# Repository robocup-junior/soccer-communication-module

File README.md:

# RCJ Soccer Communication Module

A small referee-to-robot interface for **RoboCupJunior Soccer**. A referee controls the module over **Bluetooth Low Energy (BLE)** from the mobile app, and the module relays the live match state — **PLAY, STOP, penalty, half-time, game over** — to the robot or host controller over simple digital outputs, UART, or USB serial.

The current module (board **V7 / 2026**) is built around an **ESP32-C5** and includes an OLED display, three buttons, an RGB LED, a buzzer, a USB-C port for power & flashing, and an on-board **supercapacitor** backup. It does **not** count toward the robot weight limit.

> 📦 **Got an older 2024 board?** That one uses an ESP32-**C6** — see [Legacy 2024 (ESP32-C6) modules](#-legacy-2024-esp32-c6-modules) below.

---

## 🚀 Get started

**1. Install the referee app** — Android, free on Google Play:

**➡️ [RCJ Soccer app on Google Play](https://play.google.com/store/apps/details?id=com.robocup.rcj_soccer)**

**2. Flash the module** — easiest is the **web flasher**, nothing to install:

**➡️ [Web flasher](https://robocup-junior.github.io/soccer-communication-module/)** — connect the module over USB-C and flash straight from your browser.

> The web flasher uses the Web Serial API, so use **desktop Chrome or Edge**.

**3. Wire it to your robot** — power the module from the robot battery and read one start/stop signal (see [below](#-connecting-it-to-your-robot)).

---

## 📱 Using the app

The app connects to the module over BLE and drives the whole match. The interaction pattern:

- **Double-click** for actions — e.g. double-click a robot to start/stop it, or to issue a penalty.
- **Hold** for settings — e.g. hold a robot button for connection settings.
- **Start/stop** resets all timers and starts/stops all robots at once.
- **Score:** double-click a score to add a point; hold the score number for −1.

The app's source code lives in its own repository: **[robocup-junior/soccer-referee-app](https://github.com/robocup-junior/soccer-referee-app)**.

---

## 🔌 Connecting it to your robot

### Read the start/stop signal (pick one method)

The robot must respond to the start/stop signal for the entire game. Use **one** of the following methods and react whenever the state changes:

| Method         | Pin                            | PLAY / GO        | STOP        |
|----------------|--------------------------------|------------------|-------------|
| **Output pin** | `OUT1` or `OUT2`               | **3.3 V** (HIGH) | **0 V** (LOW) |
| **UART**       | `TX0` (UART0 on the U3 header) | sends `PLAY`     | sends `STOP` |
| **USB serial** | USB-C                          | sends `PLAY`     | sends `STOP` |

Both outputs carry the same 3.3 V logic-level signal. For 5 V robot inputs, add a level shifter before the robot. Always share **GND** with the robot controller — never connect VIN to a robot GPIO or to the 3.3 V pin.

For a Raspberry Pi or another USB host, connect the module's USB-C port to the host's USB-A port. The ESP32-C5 enumerates as a serial device, typically `/dev/ttyACM0`, and prints one line (`PLAY` or `STOP`) whenever the referee app changes the match state.

On Linux, you can check the USB serial output with:

```sh
stty -F /dev/ttyACM0 115200 raw -echo
cat /dev/ttyACM0
```

The onboard buzzer gives a short confirmation beep whenever the referee app changes the match state.
The RGB status LED is dimmed green in PLAY and dimmed red when the robot output is stopped.

### Power it

Power the module **directly from the robot battery** so it stays alive for the whole match — even when the robot is switched off or removed from the field — to keep a stable BLE connection.

- **Battery:** connect **VIN** to battery **+** and **GND** to battery **−** (no switch in between). VIN accepts **4.5 V – 50 V** (the on-board buck regulator is rated higher, but RoboCupJunior rules cap robot voltage at 50 V).
- **USB-C:** the module can also run from USB-C (VBUS).
- **Regulated 3.3 V:** you may instead feed **3.3 V** to the 3V3 pin. If you do, design the supply to cover a short **startup demand of ~0.5 A at 3.3 V (≈1.65 W)**; steady-state draw is far lower.

### Supercapacitor backup

The back-side **supercapacitor** rides through short voltage dips during play (e.g. a battery sag). Switch the **supercapacitor switch ON before the match**, and **OFF when the module is not in use** so it doesn't stay charged in storage.

### Mounting

Mount the module where the **display stays visible** and the connector is **easy to reach** — typically on top of the robot via a hub, either on your own PCB or on protoboard/breadboard. We can also provide a limited number of **hub boards** you can permanently attach to your robot ([hub photo](./.readme_images/hub_image.png?raw=true)).

---

## ⏱️ During the match

### Penalties (fast & quiet)

To penalize a robot, **double-press the large button** on the module. The module sends a penalty request to the referee app, so the right robot is identified and the penalty timer starts — no shouting robot designators across the field. The firmware detects the double-press and sends the request **only while the robot is in the PLAY state**.

### Putting robots back in

The OLED shows a **countdown** for the duration of a robot's penalty. Teams may return robots to play, per the rules, once the penalty time is up on the display.

---

## 🤖 Robot-to-robot communication

Direct robot-to-robot communication is **planned for a future firmware release**. The current firmware relays the referee's match state (start/stop, penalty, half-time, game over) only — via the output pins or UART described above.

> The old 2024 board's channel-select `A0`/`A1` pins and the `LOGV` UART-level pin are **not** present on this hardware.

---

## 🛠️ Firmware & flashing (details)

For most users the [web flasher](https://robocup-junior.github.io/soccer-communication-module/) is all you need. Under the hood:

The firmware is an **ESP-IDF** project (Arduino runs as an IDF component). Releases are built automatically from Git tags matching `fw-*` or `v*` — pushing a tag makes GitHub Actions build the ESP32-C5 firmware, publish a GitHub Release with the `.bin` files, and deploy the latest web flasher to GitHub Pages:

```sh
git tag fw-v0.97
git push origin fw-v0.97
```

The release includes a single **merged image** (bootloader + partition table + app) plus the individual bins for `idf.py`/esptool users.

---

## 🧩 Legacy 2024 (ESP32-C6) modules

The older 2024 board uses an **ESP32-C6** (no USB-C connector) instead of the current ESP32-C5. It is still supported with a final, maintained firmware on the **[`legacy/esp32-c6`](https://github.com/robocup-junior/soccer-communication-module/tree/legacy/esp32-c6)** branch. Those builds are published as **GitHub Release assets** (tags `legacy-c6-*`); there is no web flasher for them.

**Flashing (native USB — recommended):** the C6's USB D+/D− are broken out on the programming header. Wire them to a USB port (the module enumerates as a serial device), then flash the merged image with full erase:

```sh
esptool --chip esp32c6 -p <PORT> write_flash --erase-all 0x0 rcj_comm_module-<ver>-merged.bin
```

A UART path also exists via the level-shifted RX/TX header pins, but it needs the `LOGV` pin powered at 3.3 V and manual download-mode entry (hold IO9/BOOT low, pulse EN), so native USB is easier. Either path can use the special flashing jig PCB.

---

## ❓ Not working?

Check the [open issues](https://github.com/robocup-junior/soccer-communication-module/issues) first and — if nobody has posted yours yet — open a [new GitHub issue](https://github.com/robocup-junior/soccer-communication-module/issues/new), post on [the forum](https://junior.forum.robocup.org/c/robocupjunior-soccer/5), or ask on the [RoboCupJunior Discord](https://discord.gg/45pxMQY4nJ).

## 🙌 Could use some help with

- An adapter hub for EV3 / SPIKE
- More component libraries (footprint / schematic / 3D) for Altium, Eagle, KiCad, EasyEDA, OrcaCAD, …
- Reporting errors & testing

## 🔭 Currently working on

- Robot-to-robot communication
- Additional RGB LED feedback patterns

## 🏆 Hall of fame

- App by Mato Faltus
- Altium lib by Youssef Shaalan

---

## 📄 Quick connection guide

A printable one-page (A5) summary of the pinout, signals, power, and wiring:

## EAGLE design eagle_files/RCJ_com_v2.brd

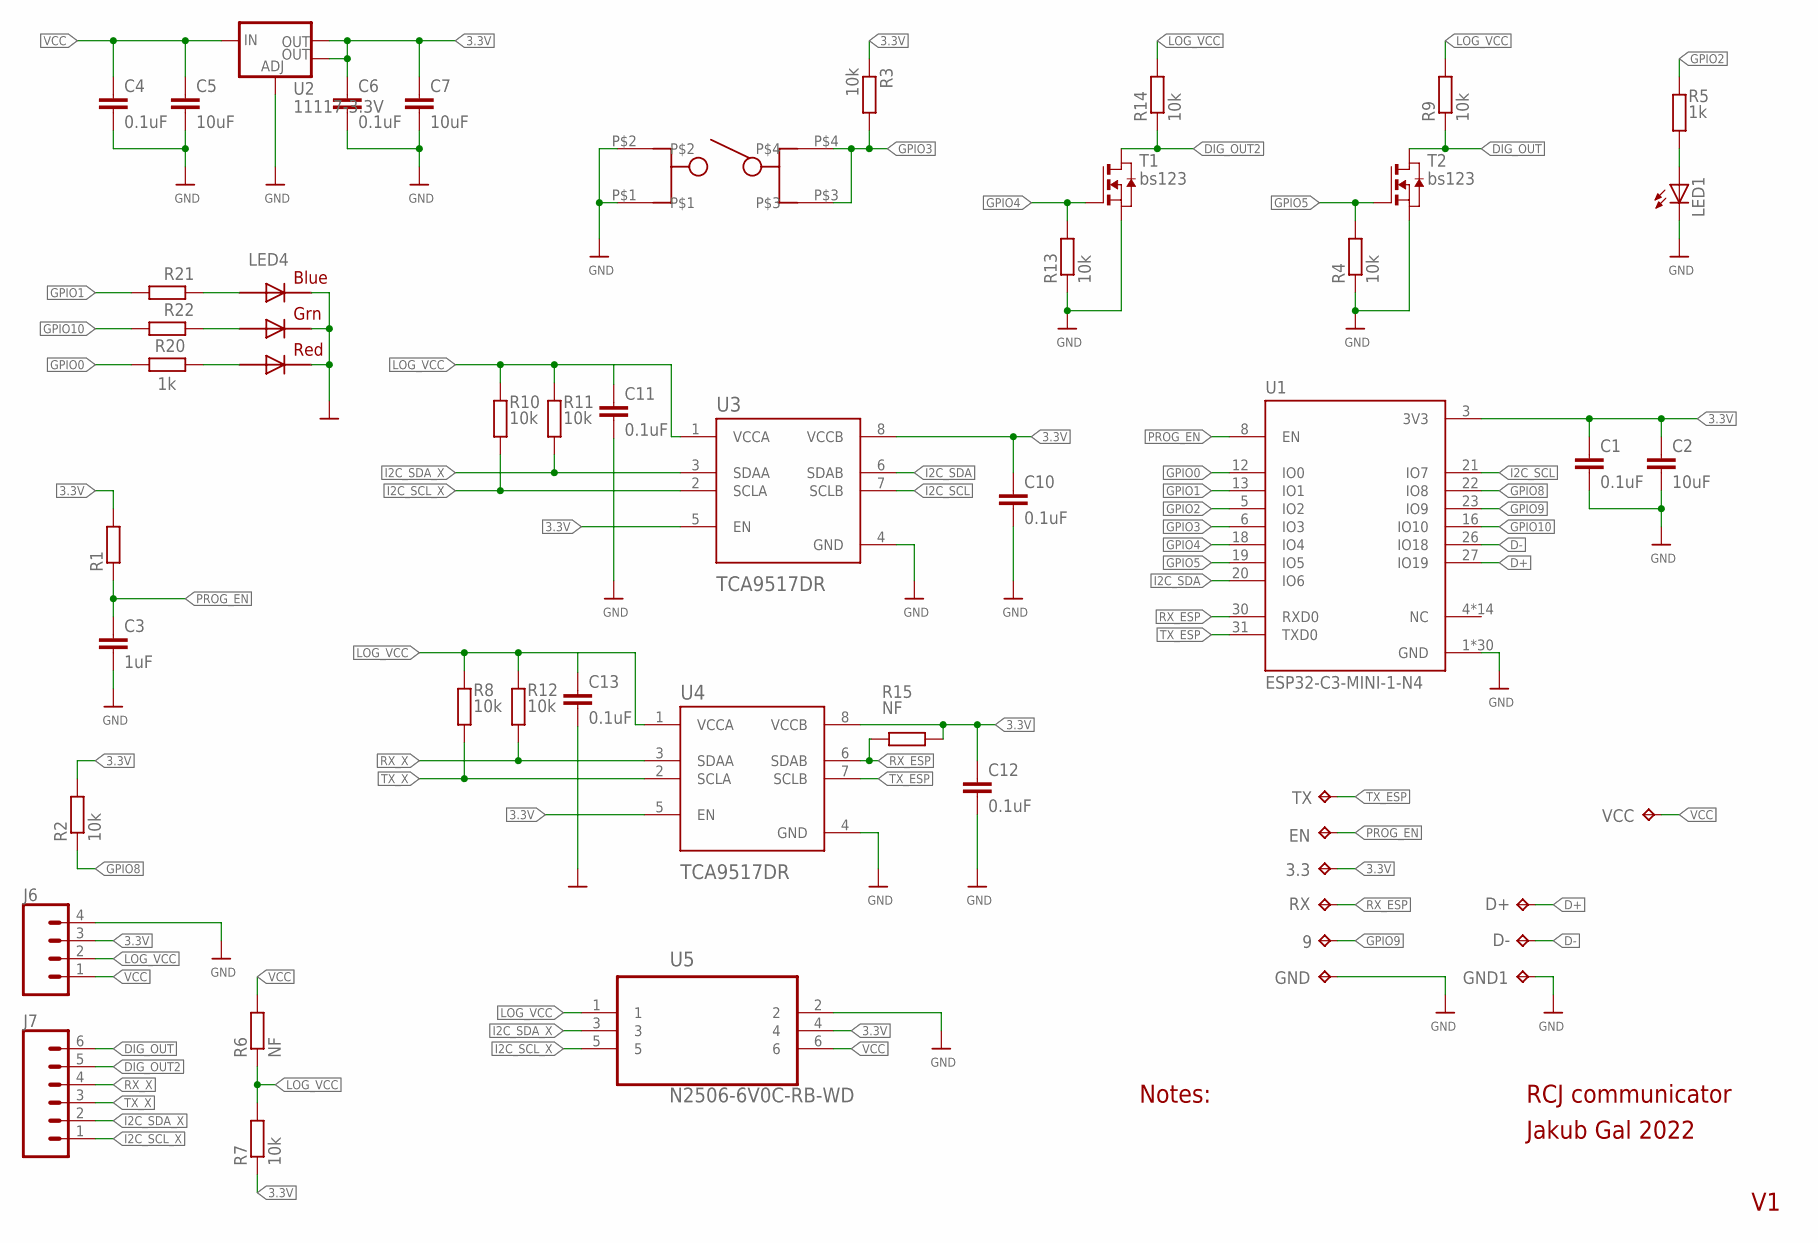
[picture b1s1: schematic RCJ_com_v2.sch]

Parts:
3.3, 9: TPTP08R; TP08R
C1, C4, C6, C10, C11, C12, C13: 0.1uF; C0402K
C2, C5, C7: 10uF; C0402K
C3: 1uF; C0402K
D+: TPTP08R; TP08R
D-: TPTP08R; TP08R
EN: TPTP08R; TP08R
GND, GND1: TPTP08R; TP08R
J6: CONN_04; 1X04
J7: CONN_06SILK_FEMALE_PTH; 1X06
LED1: 0603_Led; CHIPLED_0603
LED4: RGBLED5050
R1, R2, R3, R4, R7, R8, R9, R10, R11, R12, R13, R14: 10k; R0402
R5, R20, R21, R22: 1k; R0402
R6, R15: NF; R0402
RX: TPTP08R; TP08R
T1, T2: bs123; SOT-23
TX: TPTP08R; TP08R
U1: ESP32-C3-MINI-1-N4; XCVR_ESP32-C3-MINI-1-N4
U2: 11117-3.3V; SOT223
U3, U4: TCA9517DR; SOIC127P599X175-8N
U5: N2506-6V0C-RB-WD; 3M_N2506-6V0C-RB-WD
U$9: BUTON; PBUTON_LSCS
VCC: TPTP08R; TP08R

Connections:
3.3V: 3.3.TP, C1.1, C2.1, C6.1, C7.1, C10.1, C12.1, J6.3, R1.2, R2.2, R3.1, R7.1, R15.2, U1.3 (3V3), U2.2 (OUT), U2.4 (OUT), U3.5 (EN), U3.8 (VCCB), U4.5 (EN), U4.8 (VCCB), U5.4
D+: D+.TP, U1.27 (IO19)
D-: D-.TP, U1.26 (IO18)
DIG_OUT: J7.6, R9.1, T2.1 (D)
DIG_OUT2: J7.5, R14.1, T1.1 (D)
GND: C1.2, C2.2, C3.2, C4.2, C5.2, C6.2, C7.2, C10.2, C11.2, C12.2, C13.2, GND.TP, GND1.TP, J6.4, LED1.C, LED4.4 (BLUE_C), LED4.5 (RED_C), LED4.6 (GREEN_C), R4.1, R13.1, T1.2 (S), T2.2 (S), U1.1 (GND), U1.2 (GND), U1.11 (GND), U1.14 (GND), U1.36 (GND), U1.37 (GND), U1.38 (GND), U1.39 (GND), U1.40 (GND), U1.41 (GND), U1.42 (GND), U1.43 (GND), U1.44 (GND), U1.45 (GND), U1.46 (GND), U1.47 (GND), U1.48 (GND), U1.49_1 (GND), U1.49_2 (GND), U1.49_3 (GND), U1.49_4 (GND), U1.49_5 (GND), U1.49_6 (GND), U1.49_7 (GND), U1.49_8 (GND), U1.49_9 (GND), U1.50 (GND), U1.51 (GND), U1.52 (GND), U1.53 (GND), U2.1 (ADJ), U3.4 (GND), U4.4 (GND), U5.2, U$9.P$1, U$9.P$2
GPIO0: R20.1, U1.12 (IO0)
GPIO1: R21.1, U1.13 (IO1)
GPIO2: R5.1, U1.5 (IO2)
GPIO3: R3.2, U1.6 (IO3), U$9.P$3, U$9.P$4
GPIO4: R13.2, T1.3 (G), U1.18 (IO4)
GPIO5: R4.2, T2.3 (G), U1.19 (IO5)
GPIO8: R2.1, U1.22 (IO8)
GPIO9: 9.TP, U1.23 (IO9)
GPIO10: R22.1, U1.16 (IO10)
I2C_SCL: U1.21 (IO7), U3.7 (SCLB)
I2C_SCL_X: J7.1, R10.2, U3.2 (SCLA), U5.5
I2C_SDA: U1.20 (IO6), U3.6 (SDAB)
I2C_SDA_X: J7.2, R11.2, U3.3 (SDAA), U5.3
LOG_VCC: C11.1, C13.1, J6.2, R6.1, R7.2, R8.1, R9.2, R10.1, R11.1, R12.1, R14.2, U3.1 (VCCA), U4.1 (VCCA), U5.1
unnamed: LED1.A, R5.2
unnamed: LED4.3 (BLUE_A), R21.2
unnamed: LED4.1 (GREEN_A), R22.2
unnamed: LED4.2 (RED_A), R20.2
PROG_EN: C3.1, EN.TP, R1.1, U1.8 (EN)
RX_ESP: R15.1, RX.TP, U1.30 (RXD0), U4.6 (SDAB)
RX_X: J7.4, R12.2, U4.3 (SDAA)
TX_ESP: TX.TP, U1.31 (TXD0), U4.7 (SCLB)
TX_X: J7.3, R8.2, U4.2 (SCLA)
VCC: C4.1, C5.1, J6.1, R6.2, U2.3 (IN), U5.6, VCC.TP

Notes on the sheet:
RCJ communicator
Jakub Gal 2022
Notes:

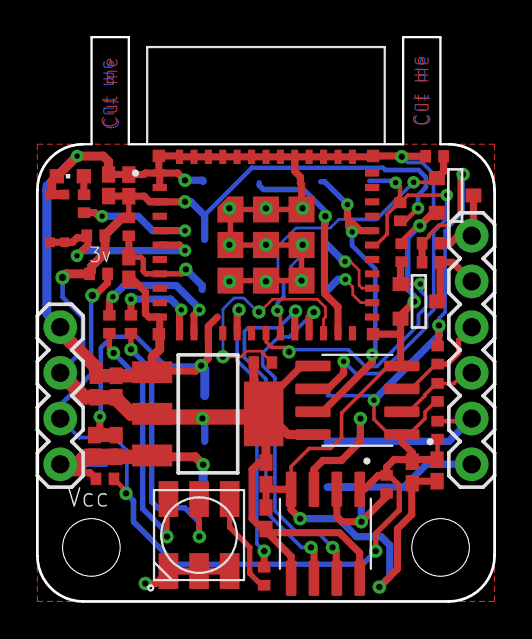
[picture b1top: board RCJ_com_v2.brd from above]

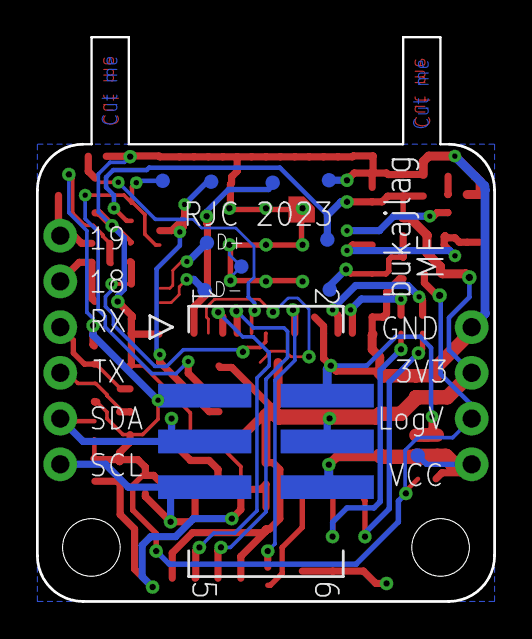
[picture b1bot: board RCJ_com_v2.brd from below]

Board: 2 copper layers, 25.4 x 31.3 mm, 51 parts (11 on the bottom side), 30 nets.

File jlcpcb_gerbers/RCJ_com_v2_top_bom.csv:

Comment,Designator,Footprint,LCSC Part #
0.1uF,C1 C4 C6 C10 C11 C12 C13,C0402K,
1k,R5 R20 R21 R22,R0402,
1uF,C3,C0402K,
10k,R1 R2 R3 R4 R7 R8 R9 R10 R11 R12 R13 R14,R0402,
10uF,C2 C5 C7,C0402K,
0603_Led,LED1,CHIPLED_0603,
11117-3.3V,U2,SOT223,
BUTON,U$9,PBUTON_LSCS,
ESP32-C3-MINI-1-N4,U1,XCVR_ESP32-C3-MINI-1-N4,
NF,R6 R15,R0402,
RGBLED5050,LED4,RGBLED5050,
TCA9517DR,U3 U4,SOIC127P599X175-8N,
bs123,T1 T2,SOT-23,

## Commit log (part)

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2024-02-25 Initial commit with information as distributed to RCJ 2023 teams
2024-03-30 Update Readme to link to Issues, Forum, Discord for problems/questions
2024-04-06 Add Bordeaux version of controller app
2024-04-10 2024_upgrade
2024-04-12 3D_model_update
2024-05-31 Fimware_update_2024_V0.1
2024-06-08 Add files via upload
    Add better image
2024-06-09 How to mount it
2024-06-14 Add eagle library
2024-06-25 aia file
2024-07-18 new_app
2024-07-18 new_fimware
2024-07-18 app_description
2024-11-20 altium_package
2025-06-13 2025 bari
2025-06-13 Create LICENSE
2025-07-13 New firmware with self penalty option
2025-07-16 Fix library problem by uncomment include
2026-03-12 add support for ESP32-C5
2026-04-29 Update BLE_NAME to include MAC address
2026-05-17 Migrate firmware to ESP-IDF Arduino component
2026-05-17 Improve BLE command latency and resilience
2026-05-18 Add firmware release workflow and web flasher
2026-05-18 Publish flasher site to gh-pages branch
2026-05-18 Use GitHub Actions Pages deployment
2026-05-18 fix: make release workflow repo explicit
    Previously the release job used gh without a checkout, which left the CLI
    unable to infer the repository. This commit passes the repository from the
    Actions context so artifact publishing works in checkout-free jobs.
    - Set `GH_REPO` for the firmware release publishing step
    - Keep the existing artifact contents and tag-triggered flow unchanged
2026-05-19 Fix ESP32-C5 web flasher reset
2026-05-19 Improve ESP32-C5 flasher reset
2026-05-19 Bump firmware version to 0.96
2026-06-04 Mirror play stop status to USB serial
2026-06-04 Add buzzer feedback for match state changes
2026-06-04 Add RGB status LED for play and stop
2026-06-04 Dim RGB status LED brightness
2026-06-30 docs: add OLED QR scan banding screenshots (issue #9)

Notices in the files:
parts and their libraries:
SparkFun-IC-Power: Licensing: Creative Commons ShareAlike 4.0 International - https://creativecommons.org/licenses/by-sa/4.0
